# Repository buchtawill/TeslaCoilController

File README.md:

# TeslaCoilController
Forked from Cather-Zhang:TeslaCoilController to support new spin of interrupter.

STM32 tesla coil controller
Up to 5 notes simultaneously reading from custom binary file format

There are three modes available:
1. SD card (read songs from SD card)
2. Burst mode
3. Fixed mode

MIT License

Copyright (c) 2023 Will Buchta, Cather Zhang

Permission is hereby granted, free of charge, to any person obtaining a copy
of this software and associated documentation files (the "Software"), to deal
in the Software without restriction, including without limitation the rights
to use, copy, modify, merge, publish, distribute, sublicense, and/or sell
copies of the Software, and to permit persons to whom the Software is
furnished to do so, subject to the following conditions:

The above copyright notice and this permission notice shall be included in all
copies or substantial portions of the Software.

THE SOFTWARE IS PROVIDED "AS IS", WITHOUT WARRANTY OF ANY KIND, EXPRESS OR
IMPLIED, INCLUDING BUT NOT LIMITED TO THE WARRANTIES OF MERCHANTABILITY,
FITNESS FOR A PARTICULAR PURPOSE AND NONINFRINGEMENT. IN NO EVENT SHALL THE
AUTHORS OR COPYRIGHT HOLDERS BE LIABLE FOR ANY CLAIM, DAMAGES OR OTHER
LIABILITY, WHETHER IN AN ACTION OF CONTRACT, TORT OR OTHERWISE, ARISING FROM,
OUT OF OR IN CONNECTION WITH THE SOFTWARE OR THE USE OR OTHER DEALINGS IN THE
SOFTWARE.

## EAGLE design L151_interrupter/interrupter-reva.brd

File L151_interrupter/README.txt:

Directory structure:
    - Core/         STM32 specific drivers
    - Debug/        STM32 build debug dir
    - Drivers/      STM32 HAL drivers 
    - FATFS/        FATFS used for STM32 SD card
    - fusion360/    Interrupter case 3d files
    - Middlewares/  FATFS and USB stuff
    - USB_DEVICE/   STM32 USB drivers

Important notes:
    The program assumes that the SD card has .will formatted files in two directories:
        - single_coil/
        - dual_coils/
    Upon boot, the STM32 reads and stores all filenames from both these directories.
    Filenames are limited to 64 characters, including extension
    Up to 32 files can be in each directory (Fix this in the future)

    Need to enable "#define _FS_RPATH 1" in L151_interrupter\FATFS\Target\ffconf.h to enable "chdir()" function

    Setting A sets ONLY A 
    But setting B sets a and B

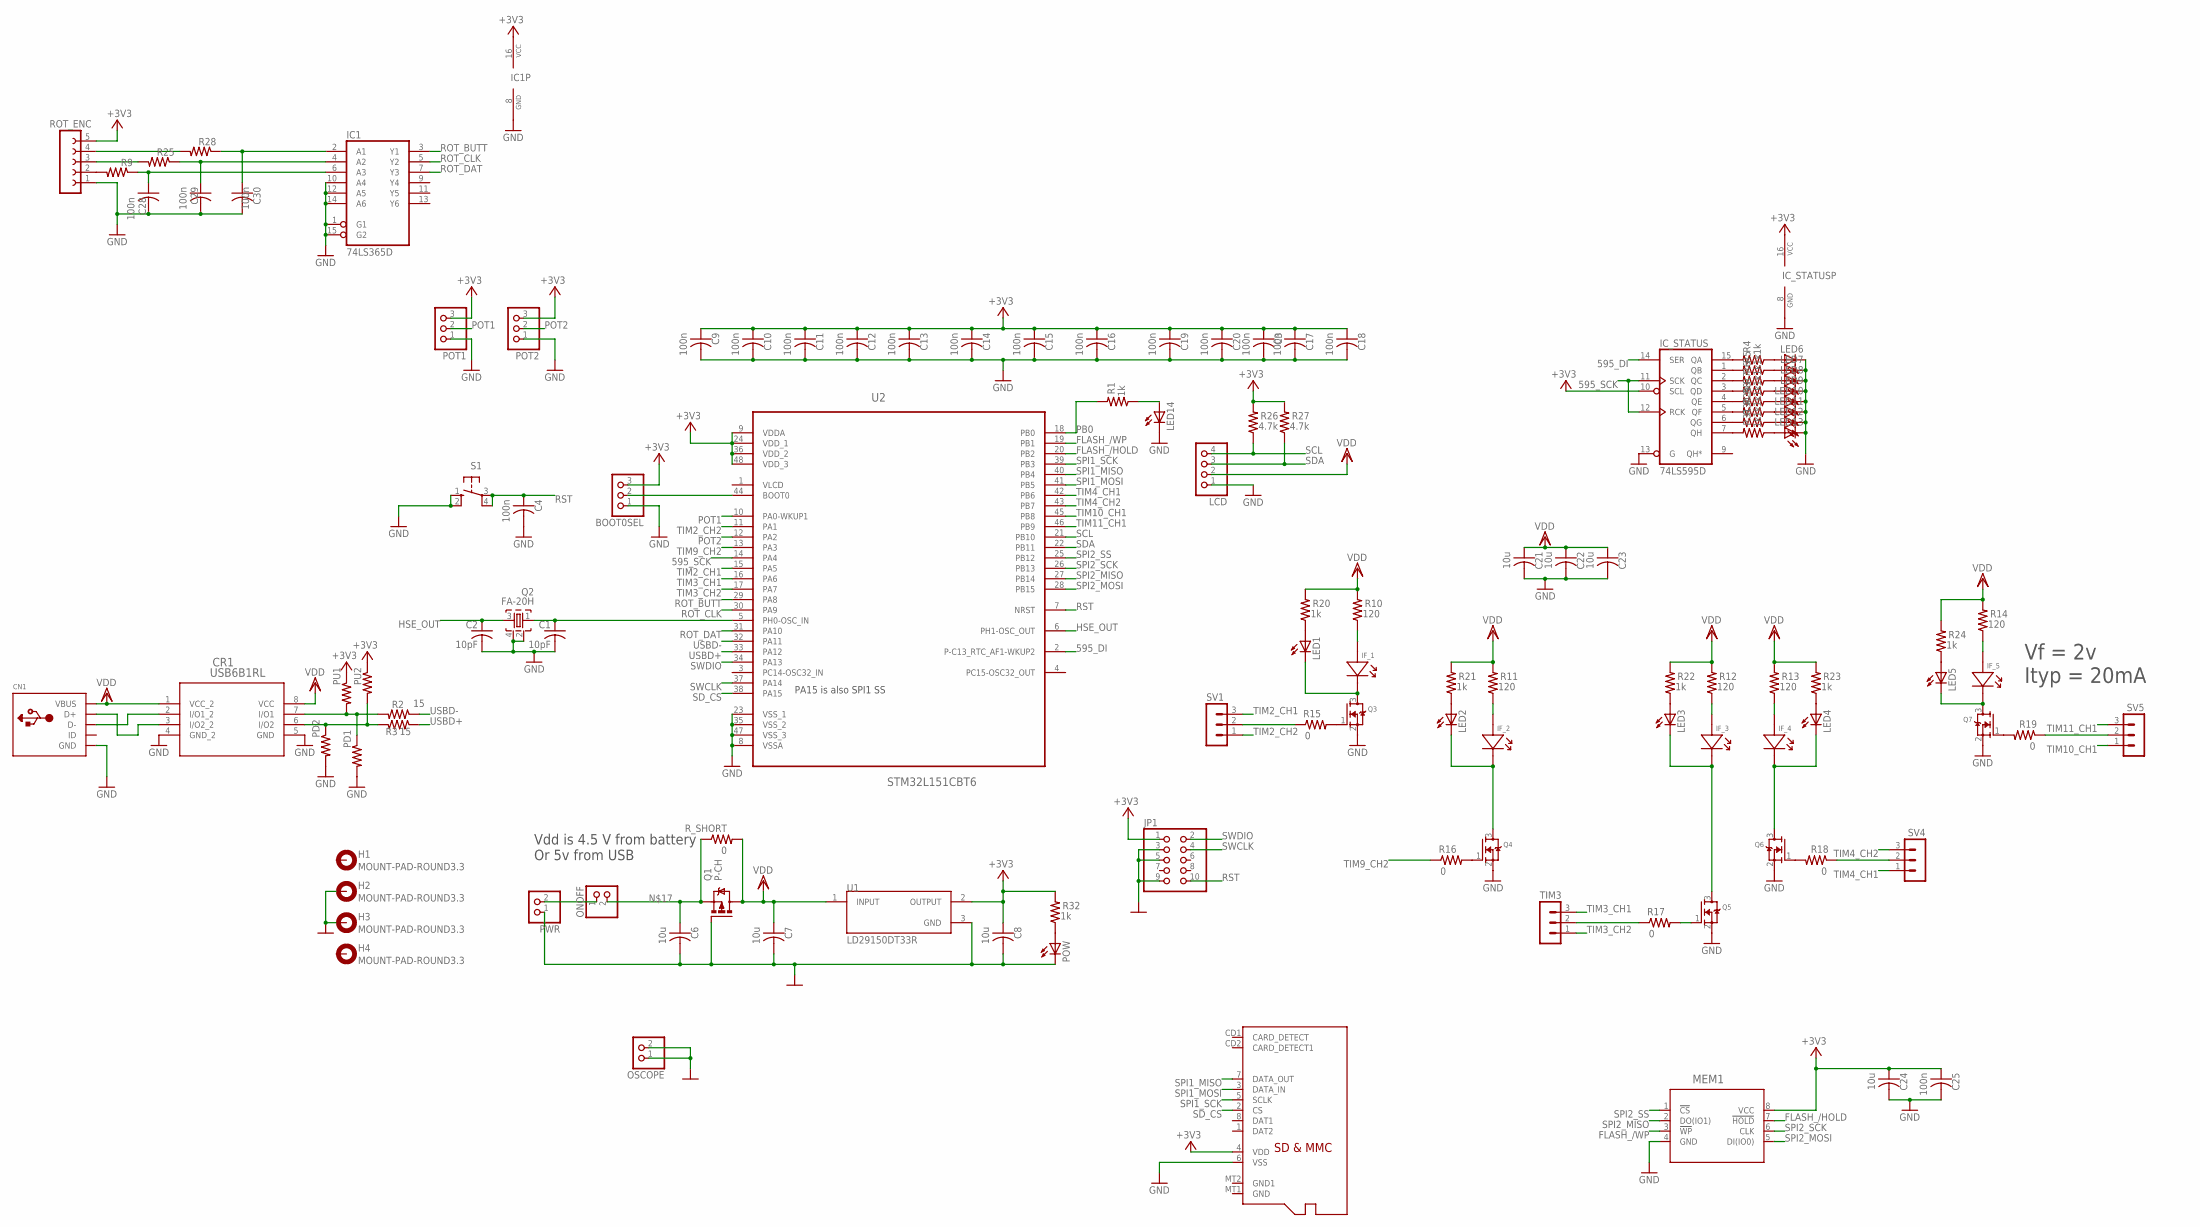
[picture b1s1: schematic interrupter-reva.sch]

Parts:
BOOT0SEL: PINHD-1X3; 1X03
C1, C2: 10pF; C0603
C3, C9, C11, C13, C15, C17, C20, C25: 100n; C0805
C4: 100n; C0402
C6, C7, C21, C22, C23: 10u; C0805
C8, C24: 10u; C0603
C10, C12, C14, C16, C18, C19, C28, C29, C30: 100n; C0603
CN1: USBMINIB; USB-MINIB
CR1: USB6B1RL; SO-8_STM
H1, H2, H3, H4: MOUNT-PAD-ROUND3.3; 3,3-PAD
IC1: 74LS365D; SO16
IC_STATUS: 74LS595D; SO16
IF_1, IF_2, IF_3, IF_4, IF_5: IF-E96E
JP1: PINHD-2X5; 2X05
LCD: PINHD-1X4; 1X04
LED1, LED2, LED3, LED4, LED5, LED6, LED7, LED8, LED9, LED10, LED11, LED12, LED13, LED14: LEDCHIP-LED0805; CHIP-LED0805
MEM1: W25X40CLSNIG; WIN_SN-8_WIN
ONOFF: PINHD-1X2; 1X02
OSCOPE: PINHD-1X2; 1X02
PD1, PD2: 15; R0603
POT1, POT2: PINHD-1X3; 1X03
POW: LEDCHIP-LED0805; CHIP-LED0805
PU1, PU2: 15; R0603
PWR: PINHD-1X2; 1X02
Q1: P-CH; MICRO3
Q2: FA-20H
Q3, Q4, Q5, Q6, Q7: MOSFET-NREFLOW; SOT23
R1, R4, R5, R6, R7, R8, R29, R30, R31, R32: 1k; R0603
R2, R3: 15; R0603
R9, R25, R28: R-US_R0603; R0603
R10, R11, R12, R13, R14: 120; R0805
R15, R16, R17, R18, R19: 0; R0805
R20, R21, R22, R23, R24: 1k; R0805
R26, R27: 4.7k; R0805
ROT_ENC: FE05-1
R_SHORT: 0; R0805
S1: 10-XX; B3F-10XX
SV1, SV4, SV5: MA03-1
TIM3: MA03-1
U1: LD29150DT33R; DPAK456P972X240-3N
U2: STM32L151CBT6; QFP50P900X900X160-48N
U$1: MICROSD

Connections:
595_DI: IC_STATUS.14 (SER), U2.2 (P-C13_RTC_AF1-WKUP2)
595_SCK: IC_STATUS.11 (SCK), IC_STATUS.12 (RCK), U2.14 (PA4)
+3V3: BOOT0SEL.3, C3.1, C8.1, C9.1, C10.1, C11.1, C12.1, C13.1, C14.1, C15.1, C16.1, C17.1, C18.1, C19.1, C20.1, C24.1, C25.1, IC1.16 (VCC), IC_STATUS.10 (SCL), IC_STATUS.16 (VCC), JP1.1, MEM1.8 (VCC), POT1.3, POT2.3, PU1.1, PU2.1, R26.2, R27.2, R32.2, ROT_ENC.5, U1.2 (OUTPUT), U2.9 (VDDA), U2.24 (VDD_1), U2.36 (VDD_2), U2.48 (VDD_3), U$1.4 (VDD)
FLASH_/HOLD: MEM1.7 (!HOLD), U2.20 (PB2)
FLASH_/WP: MEM1.3 (!WP), U2.19 (PB1)
GND: BOOT0SEL.1, C1.2, C2.2, C3.2, C4.2, C6.2, C7.2, C8.2, C9.2, C10.2, C11.2, C12.2, C13.2, C14.2, C15.2, C16.2, C17.2, C18.2, C19.2, C20.2, C21.2, C22.2, C23.2, C24.2, C25.2, C28.2, C29.2, C30.2, CN1.GND, CR1.4 (GND_2), CR1.5 (GND), H2.B3,3, H3.B3,3, IC1.1 (G1), IC1.8 (GND), IC1.10 (A4), IC1.12 (A5), IC1.14 (A6), IC1.15 (G2), IC_STATUS.8 (GND), IC_STATUS.13 (G), JP1.3, JP1.5, JP1.9, LCD.1, LED6.C, LED7.C, LED8.C, LED9.C, LED10.C, LED11.C, LED12.C, LED13.C, LED14.C, MEM1.4 (GND), OSCOPE.1, OSCOPE.2, PD1.2, PD2.2, POT1.1, POT2.1, POW.C, PWR.1, Q1.1 (G), Q2.2, Q2.4, Q3.2 (S), Q4.2 (S), Q5.2 (S), Q6.2 (S), Q7.2 (S), ROT_ENC.1, S1.1 (S), S1.2 (S1), U1.3 (GND), U2.8 (VSSA), U2.23 (VSS_1), U2.35 (VSS_2), U2.47 (VSS_3), U$1.6 (VSS)
HSE_OUT: C2.1, Q2.3, U2.6 (PH1-OSC_OUT)
unnamed: R9.2, ROT_ENC.2
unnamed: LED1.A, R20.1
unnamed: CN1.D-, CR1.2 (I/O1_2)
unnamed: LED2.A, R21.1
unnamed: LED3.A, R22.1
unnamed: LED5.A, R24.1
unnamed: IF_1.ANODE, R10.1
unnamed: IF_2.ANODE, R11.1
unnamed: IF_3.ANODE, R12.1
unnamed: IF_4.ANODE, R13.1
unnamed: IF_5.ANODE, R14.1
unnamed: IF_1.CATHODE, LED1.C, Q3.3 (D)
unnamed: IF_2.CATHODE, LED2.C, Q4.3 (D)
unnamed: IF_3.CATHODE, LED3.C, Q5.3 (D)
unnamed: IF_4.CATHODE, LED4.C, Q6.3 (D)
unnamed: IF_5.CATHODE, LED5.C, Q7.3 (D)
unnamed: C6.1, ONOFF.2, Q1.2 (S), R_SHORT.1
unnamed: ONOFF.1, PWR.2
unnamed: CN1.D+, CR1.3 (I/O2_2)
unnamed: CR1.7 (I/O1), PD1.1, PU1.2, R2.2
unnamed: R25.2, ROT_ENC.3
unnamed: Q7.1 (G), R19.2
unnamed: R28.2, ROT_ENC.4
unnamed: CR1.6 (I/O2), PD2.1, PU2.2, R3.2
unnamed: LED4.A, R23.1
unnamed: C28.1, IC1.6 (A3), R9.1
unnamed: C29.1, IC1.4 (A2), R25.1
unnamed: C30.1, IC1.2 (A1), R28.1
unnamed: LED6.A, R4.1
unnamed: IC_STATUS.15 (QA), R4.2
unnamed: C1.1, Q2.1, U2.5 (PH0-OSC_IN)
unnamed: LED7.A, R5.1
unnamed: IC_STATUS.1 (QB), R5.2
unnamed: LED8.A, R6.1
unnamed: IC_STATUS.2 (QC), R6.2
unnamed: LED9.A, R7.1
unnamed: IC_STATUS.3 (QD), R7.2
unnamed: LED10.A, R8.1
unnamed: IC_STATUS.4 (QE), R8.2
unnamed: LED11.A, R29.1
unnamed: IC_STATUS.5 (QF), R29.2
unnamed: LED12.A, R30.1
unnamed: IC_STATUS.6 (QG), R30.2
unnamed: BOOT0SEL.2, U2.44 (BOOT0)
unnamed: R15.1, SV1.2
unnamed: Q3.1 (G), R15.2
unnamed: Q4.1 (G), R16.2
unnamed: LED13.A, R31.1
unnamed: Q5.1 (G), R17.2
unnamed: R17.1, TIM3.2
unnamed: Q6.1 (G), R18.2
unnamed: R18.1, SV4.2
unnamed: R19.1, SV5.2
unnamed: IC_STATUS.7 (QH), R31.2
unnamed: LED14.A, R1.1
unnamed: POW.A, R32.1
PB0: R1.2, U2.18 (PB0)
POT1: POT1.2, U2.10 (PA0-WKUP1)
POT2: POT2.2, U2.12 (PA2)
ROT_BUTT: IC1.3 (Y1), U2.29 (PA8)
ROT_CLK: IC1.5 (Y2), U2.30 (PA9)
ROT_DAT: IC1.7 (Y3), U2.31 (PA10)
RST: C4.1, JP1.10, S1.3, S1.4 (P1), U2.7 (NRST)
SCL: LCD.4, R26.1, U2.21 (PB10)
SDA: LCD.3, R27.1, U2.22 (PB11)
SD_CS: U2.38 (PA15), U$1.2 (CS)
SPI1_MISO: U2.40 (PB4), U$1.7 (DATA_OUT)
SPI1_MOSI: U2.41 (PB5), U$1.3 (DATA_IN)
SPI1_SCK: U2.39 (PB3), U$1.5 (SCLK)
SPI2_MISO: MEM1.2 (DO(IO1)), U2.27 (PB14)
SPI2_MOSI: MEM1.5 (DI(IO0)), U2.28 (PB15)
SPI2_SCK: MEM1.6 (CLK), U2.26 (PB13)
SPI2_SS: MEM1.1 (!CS), U2.25 (PB12)
SWCLK: JP1.4, U2.37 (PA14)
SWDIO: JP1.2, U2.34 (PA13)
TIM2_CH1: SV1.3, U2.15 (PA5)
TIM2_CH2: SV1.1, U2.11 (PA1)
TIM3_CH1: TIM3.3, U2.16 (PA6)
TIM3_CH2: TIM3.1, U2.17 (PA7)
TIM4_CH1: SV4.1, U2.42 (PB6)
TIM4_CH2: SV4.3, U2.43 (PB7)
TIM9_CH2: R16.1, U2.13 (PA3)
TIM10_CH1: SV5.1, U2.45 (PB8)
TIM11_CH1: SV5.3, U2.46 (PB9)
USBD+: R3.1, U2.33 (PA12)
USBD-: R2.1, U2.32 (PA11)
VDD: C7.1, C21.1, C22.1, C23.1, CN1.VBUS, CR1.1 (VCC_2), CR1.8 (VCC), LCD.2, Q1.3 (D), R10.2, R11.2, R12.2, R13.2, R14.2, R20.2, R21.2, R22.2, R23.2, R24.2, R_SHORT.2, U1.1 (INPUT)
VLCD: U2.1 (VLCD)

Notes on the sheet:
Vf = 2v Ityp = 20mA
Vdd is 4.5 V from battery Or 5v from USB
PA15 is also SPI1 SS

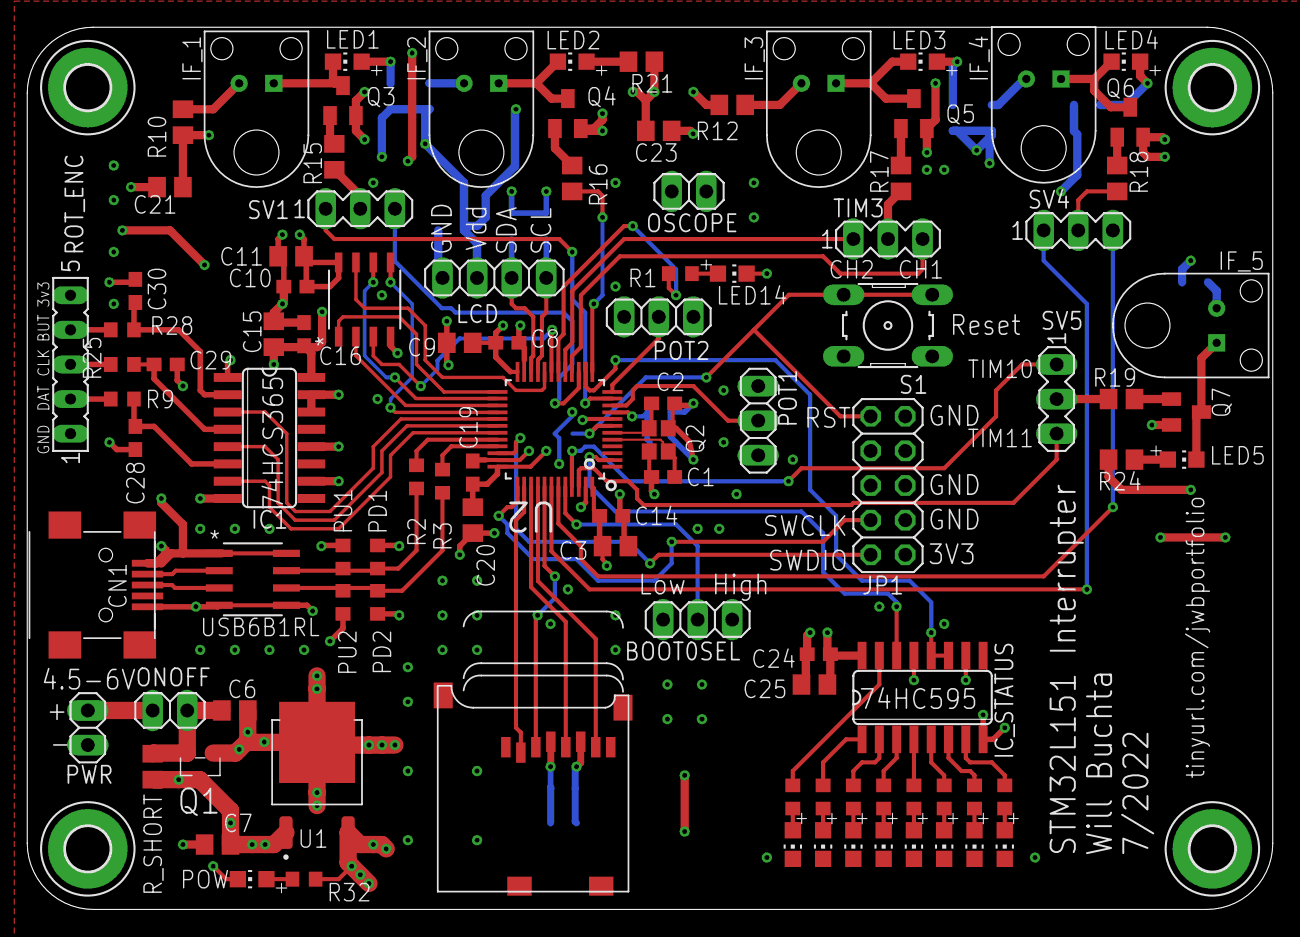
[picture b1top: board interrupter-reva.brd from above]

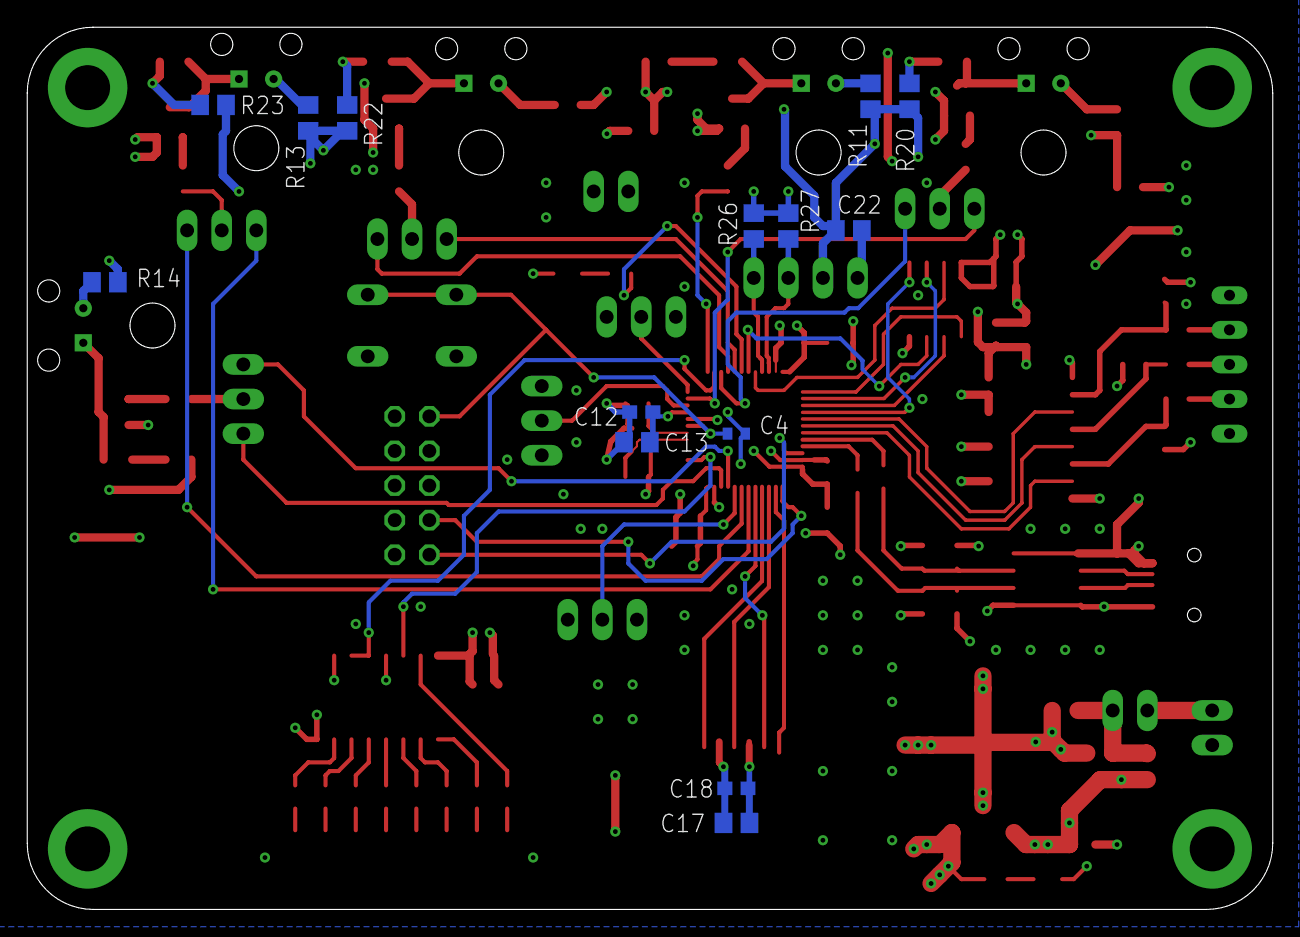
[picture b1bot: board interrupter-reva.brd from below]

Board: 4 copper layers, 91.4 x 64.8 mm, 117 parts (14 on the bottom side), 94 nets.

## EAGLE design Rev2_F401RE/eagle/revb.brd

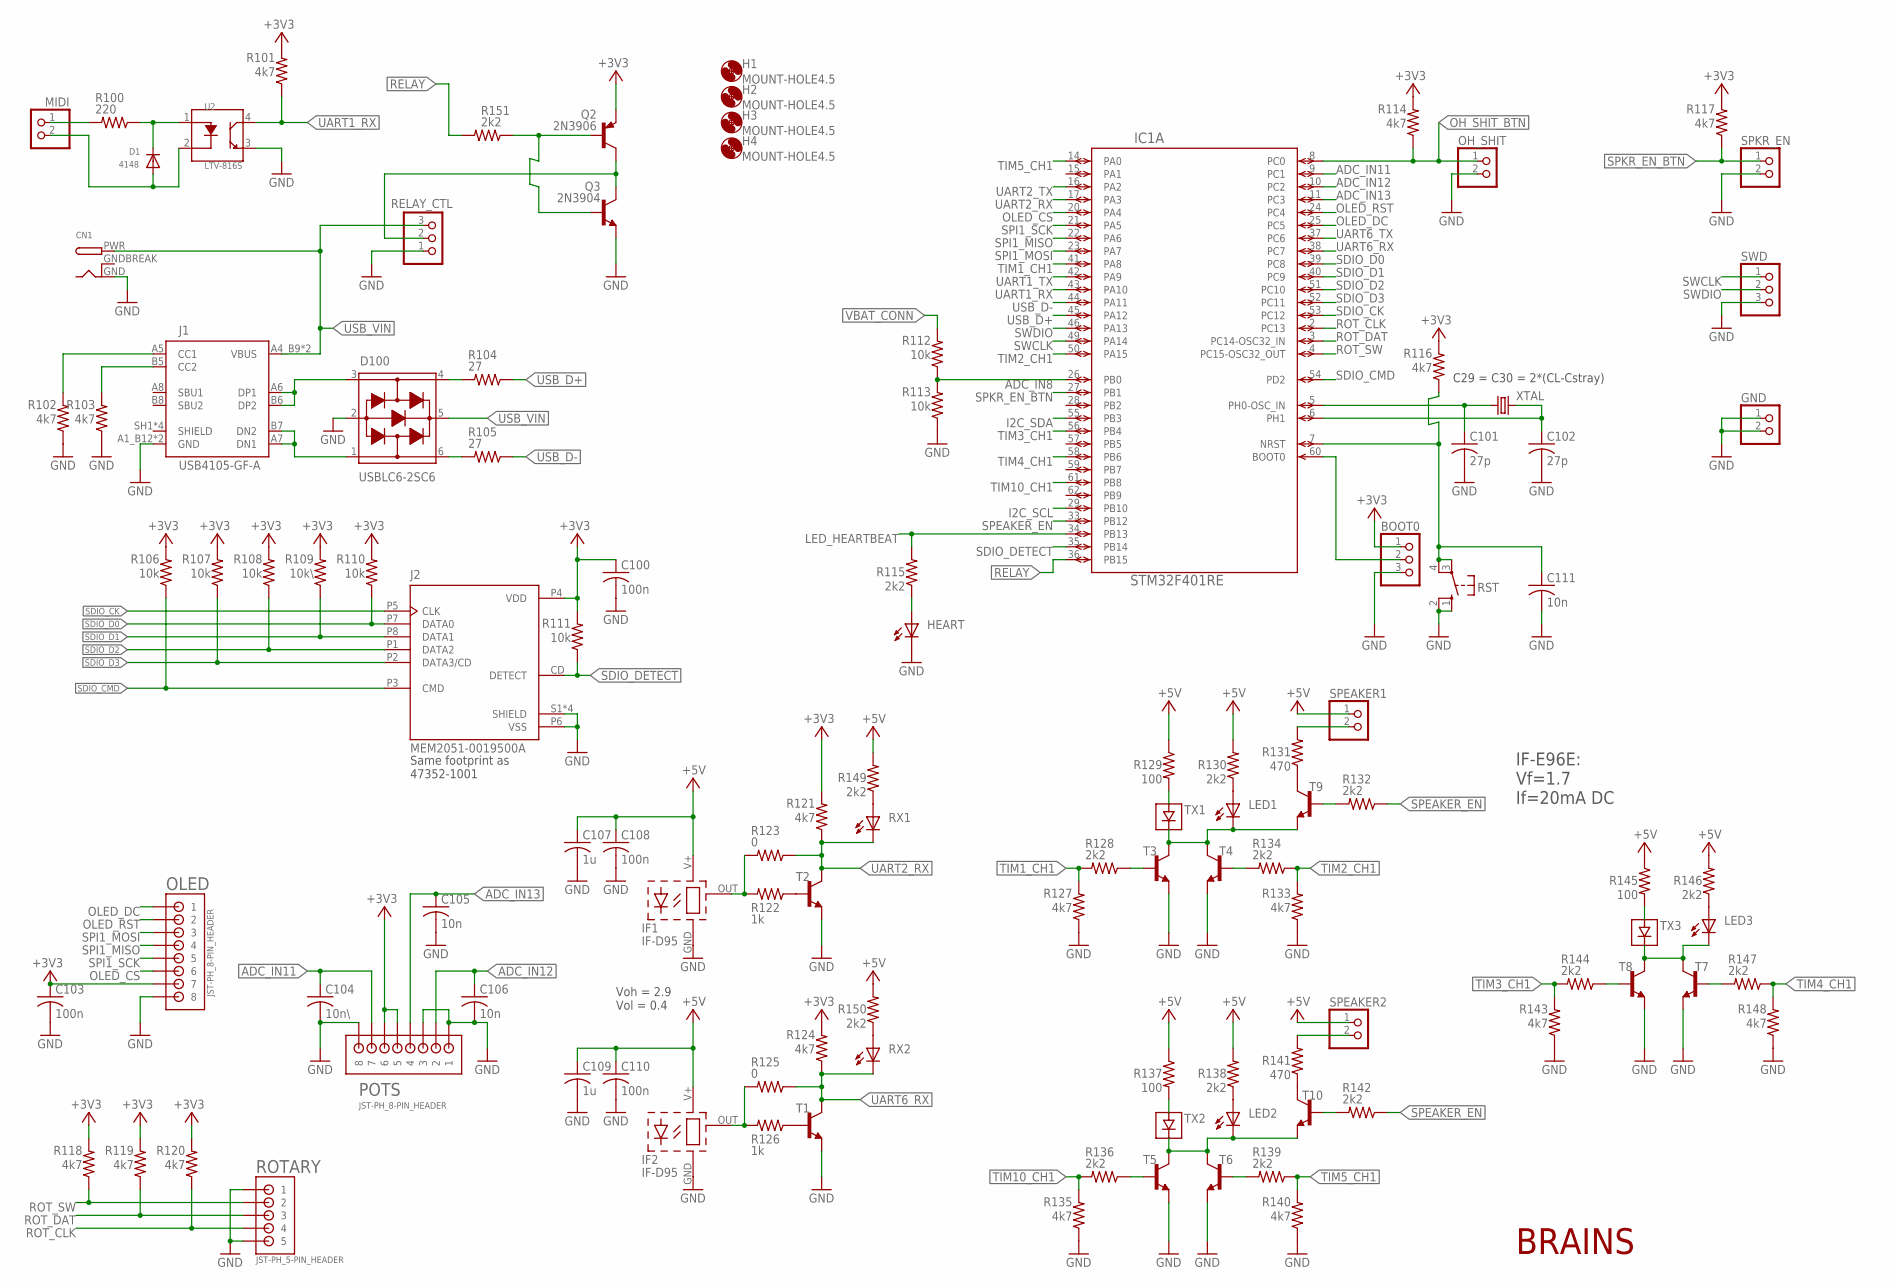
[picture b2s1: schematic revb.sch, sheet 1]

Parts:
BOOT0: PINHD-1X3; 1X03
C100, C103, C108, C110: 100n; C0603K
C101, C102: 27p; C0402
C104: 10n\; C0603K
C105, C106, C111: 10n; C0603K
C107, C109: 1u; C0603K
CN1: DCBARRELPTH; DCJACK_2MM_PTH
D1: 4148; SOD-123
D100: USBLC6-2SC6; SOT95P280X145-6N
GND: PINHD-1X2; 1X02
H1, H2, H3, H4: MOUNT-HOLE4.5; 4,5
HEART: LEDCHIPLED_0805; CHIPLED_0805
IC1: STM32F401RE; LQFP64-10X10MM
IF1, IF2: IF-D95; IFD95
J1: USB4105-GF-A; GCT_USB4105-GF-A
J2: MEM2051-0019500A; GCT_MEM2051-00-195-00-A_REVD1
LED1, LED2, LED3: LEDCHIPLED_0805; CHIPLED_0805
MIDI: PINHD-1X2; 1X02
OH_SHIT: PINHD-1X2; 1X02
OLED: JST-PH_8-PIN_HEADER; JST_B8B-PH_HEADER
POTS: JST-PH_8-PIN_HEADER; JST_B8B-PH_HEADER
Q2: 2N3906; TO92
Q3: 2N3904; TO92
R100: 220; R0603
R101, R102, R103, R114, R116, R117, R118, R119, R120, R121, R124, R127, R133, R135, R140, R143, R148: 4k7; R0603
R104, R105: 27; R0603
R106, R107, R108, R110, R111, R112, R113: 10k; R0805
R109: 10k\; R0805
R115, R128, R130, R132, R134, R136, R138, R139, R142, R144, R146, R147, R149, R150, R151: 2k2; R0603
R122, R126: 1k; R0805
R123, R125: 0; R0603
R129, R137, R145: 100; R0805
R131, R141: 470; R0603
RELAY_CTL: PINHD-1X3; 1X03
ROTARY: JST-PH_5-PIN_HEADER; JST_B5B-PH_HEADER
RST: 10-XX; B3F-10XX
RX1, RX2: LEDCHIPLED_0805; CHIPLED_0805
SPEAKER1, SPEAKER2: PINHD-1X2; 1X02
SPKR_EN: PINHD-1X2; 1X02
SWD: PINHD-1X3; 1X03
T1, T2, T3, T4, T5, T6, T7, T8, T9, T10: MMBTA06-7-F; SOT23-BEC
TX1, TX2, TX3: IF-E95E; IF-E96E
U2: LTV-816S; SMD4-2.54-4.6X6.5MM
XTAL: CRYSTALHC49S; HC49/S

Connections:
+3V3: BOOT0.1, C100.1, C103.1, J2.P4 (VDD), OLED.P7 (7), POTS.P5 (5), POTS.P6 (6), Q2.3 (E), R101.2, R106.2, R107.2, R108.2, R109.2, R110.2, R111.2, R114.2, R116.2, R117.2, R118.2, R119.2, R120.2, R121.2, R124.2; also elsewhere on the board
+5V: C107.1, C108.1, C109.1, C110.1, IF1.V+ (VCC), IF2.V+ (VCC), R129.1, R130.2, R137.1, R138.2, R145.1, R146.2, R149.2, R150.2, SPEAKER1.1, SPEAKER2.1; also elsewhere on the board
ADC_IN8: IC1.26 (PB0), R112.1, R113.2
ADC_IN11: C104.1, IC1.9 (PC1), POTS.P7 (7)
ADC_IN12: C106.1, IC1.10 (PC2), POTS.P2 (2)
ADC_IN13: C105.1, IC1.11 (PC3), POTS.P4 (4)
BOOT0_CONN: BOOT0.2, IC1.60 (BOOT0)
CC1: J1.A5 (CC1), R102.2
CC2: J1.B5 (CC2), R103.2
COIL1_B: R128.1, T3.B
COIL1_NEG: LED1.C, T3.C, T4.C, T9.E, TX1.GND
COIL1_POS: R129.2, TX1.SIG
COIL2_B: R136.1, T5.B
COIL2_NEG: LED2.C, T5.C, T6.C, T10.E, TX2.GND
COIL2_POS: R137.2, TX2.SIG
COIL3_B: R144.1, T8.B
COIL3_NEG: LED3.C, T7.C, T8.C, TX3.GND
COIL3_POS: R145.2, TX3.SIG
COIL12_B: R134.2, T4.B
COIL22_B: R139.2, T6.B
COIL32_B: R147.2, T7.B
GND: BOOT0.3, C100.2, C101.2, C102.2, C103.2, C104.2, C105.2, C106.2, C107.2, C108.2, C109.2, C110.2, C111.2, CN1.GND, D100.2 (GND), GND.1, GND.2, HEART.C, IF1.GND, IF2.GND, J1.A1_B12 (GND), J1.B1_A12 (GND), J2.P6 (VSS), J2.S1 (SHIELD), J2.S2 (SHIELD), J2.S3 (SHIELD), J2.S4 (SHIELD), OH_SHIT.2, OLED.P8 (8), POTS.P1 (1), POTS.P3 (3), POTS.P8 (8), Q3.3 (E), R102.1, R103.1, R113.1, R127.1, R133.1, R135.1, R140.1, R143.1, R148.1, RELAY_CTL.1, ROTARY.P1 (1), ROTARY.P5 (5), RST.1 (S), RST.2 (S1), SPKR_EN.2, SWD.3, T1.E, T2.E, T3.E, T4.E, T5.E, T6.E, T7.E, T8.E, U2.3 (EMITER); also elsewhere on the board
GNDBREAK: CN1.GNDBREAK
I2C_SCL: IC1.29 (PB10); also elsewhere on the board
I2C_SDA: IC1.55 (PB3); also elsewhere on the board
IF1-OUT: IF1.OUT, R122.2, R123.2
IF2-OUT: IF2.OUT, R125.2, R126.2
LED_HEARTBEAT: IC1.34 (PB13), R115.2
LTV+: D1.C, R100.1, U2.1 (ANODE)
LTV-: D1.A, MIDI.2, U2.2 (CATHODE)
MID_RX_IN: MIDI.1, R100.2
unnamed: LED1.A, R130.1
unnamed: R122.1, T2.B
unnamed: LED3.A, R146.1
unnamed: LED2.A, R138.1
unnamed: R149.1, RX1.A
unnamed: R150.1, RX2.A
unnamed: R126.1, T1.B
unnamed: R131.1, T9.C
unnamed: R141.1, T10.C
NRST: C111.1, IC1.7 (NRST), R116.1, RST.3, RST.4 (P1)
OH_SHIT_BTN: IC1.8 (PC0), OH_SHIT.1, R114.1
OLED_CS: IC1.20 (PA4), OLED.P6 (6)
OLED_DC: IC1.25 (PC5), OLED.P1 (1)
OLED_RST: IC1.24 (PC4), OLED.P2 (2)
R-HB: HEART.A, R115.1
RELAY: IC1.36 (PB15), R151.2
RELAY_OUT: Q2.1 (C), Q3.1 (C), RELAY_CTL.2
RLY_BASE: Q2.2 (B), Q3.2 (B), R151.1
ROT_CLK: IC1.2 (PC13), R120.1, ROTARY.P4 (4)
ROT_DAT: IC1.3 (PC14-OSC32_IN), R119.1, ROTARY.P3 (3)
ROT_SW: IC1.4 (PC15-OSC32_OUT), R118.1, ROTARY.P2 (2)
SDIO_CK: IC1.53 (PC12), J2.P5 (CLK)
SDIO_CMD: IC1.54 (PD2), J2.P3 (CMD), R106.1
SDIO_D0: IC1.39 (PC8), J2.P7 (DATA0), R110.1
SDIO_D1: IC1.40 (PC9), J2.P8 (DATA1), R109.1
SDIO_D2: IC1.51 (PC10), J2.P1 (DATA2), R108.1
SDIO_D3: IC1.52 (PC11), J2.P2 (DATA3/CD), R107.1
SDIO_DETECT: IC1.35 (PB14), J2.CD (DETECT), R111.1
SHIELD: J1.SH1 (SHIELD), J1.SH2 (SHIELD), J1.SH3 (SHIELD), J1.SH4 (SHIELD)
SPEAK1-R: R131.2, SPEAKER1.2
SPEAKER_EN: IC1.33 (PB12), R132.1, R142.1
SPI1_MISO: IC1.22 (PA6), OLED.P4 (4)
SPI1_MOSI: IC1.23 (PA7), OLED.P3 (3)
SPI1_SCK: IC1.21 (PA5), OLED.P5 (5)
SPK2_R: R141.2, SPEAKER2.2
SPKR_EN_BTN: IC1.27 (PB1), R117.1, SPKR_EN.1
SPK_EN1_B: R132.2, T9.B
SPK_EN2_B: R142.2, T10.B
SWCLK: IC1.49 (PA14), SWD.1
SWDIO: IC1.46 (PA13), SWD.2
TIM1_CH1: IC1.41 (PA8), R127.2, R128.2
TIM2_CH1: IC1.50 (PA15), R133.2, R134.1
TIM3_CH1: IC1.56 (PB4), R143.2, R144.2
TIM4_CH1: IC1.58 (PB6), R147.1, R148.2
TIM5_CH1: IC1.14 (PA0), R139.1, R140.2
TIM10_CH1: IC1.61 (PB8), R135.2, R136.2
UART1_RX: IC1.43 (PA10), R101.1, U2.4 (COLLECTOR)
UART1_TX: IC1.42 (PA9)
UART2_RX: IC1.17 (PA3), R121.1, R123.1, RX1.C, T2.C
UART2_TX: IC1.16 (PA2)
UART6_RX: IC1.38 (PC7), R124.1, R125.1, RX2.C, T1.C
UART6_TX: IC1.37 (PC6)
USBDN_CONN: D100.1 (I/O1_IN), J1.A7 (DN1), J1.B7 (DN2)
USBDP_CONN: D100.3 (I/O2_IN), J1.A6 (DP1), J1.B6 (DP2)
USBRESD_N: D100.6 (I/O1_OUT), R105.2
USBRESD_P: D100.4 (I/O2_OUT), R104.2
USB_D+: IC1.45 (PA12), R104.1
USB_D-: IC1.44 (PA11), R105.1
USB_VIN: CN1.PWR, D100.5 (VBUS), J1.A4_B9 (VBUS), J1.B4_A9 (VBUS), RELAY_CTL.3; also elsewhere on the board
VBAT_CONN: R112.2; also elsewhere on the board
XTAL1: C101.1, IC1.5 (PH0-OSC_IN), XTAL.1
XTAL2: C102.1, IC1.6 (PH1), XTAL.2

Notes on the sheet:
BRAINS
C29 = C30 = 2*(CL-Cstray)
IF-E96E: Vf=1.7 If=20mA DC
Voh = 2.9 Vol = 0.4
Same footprint as 47352-1001

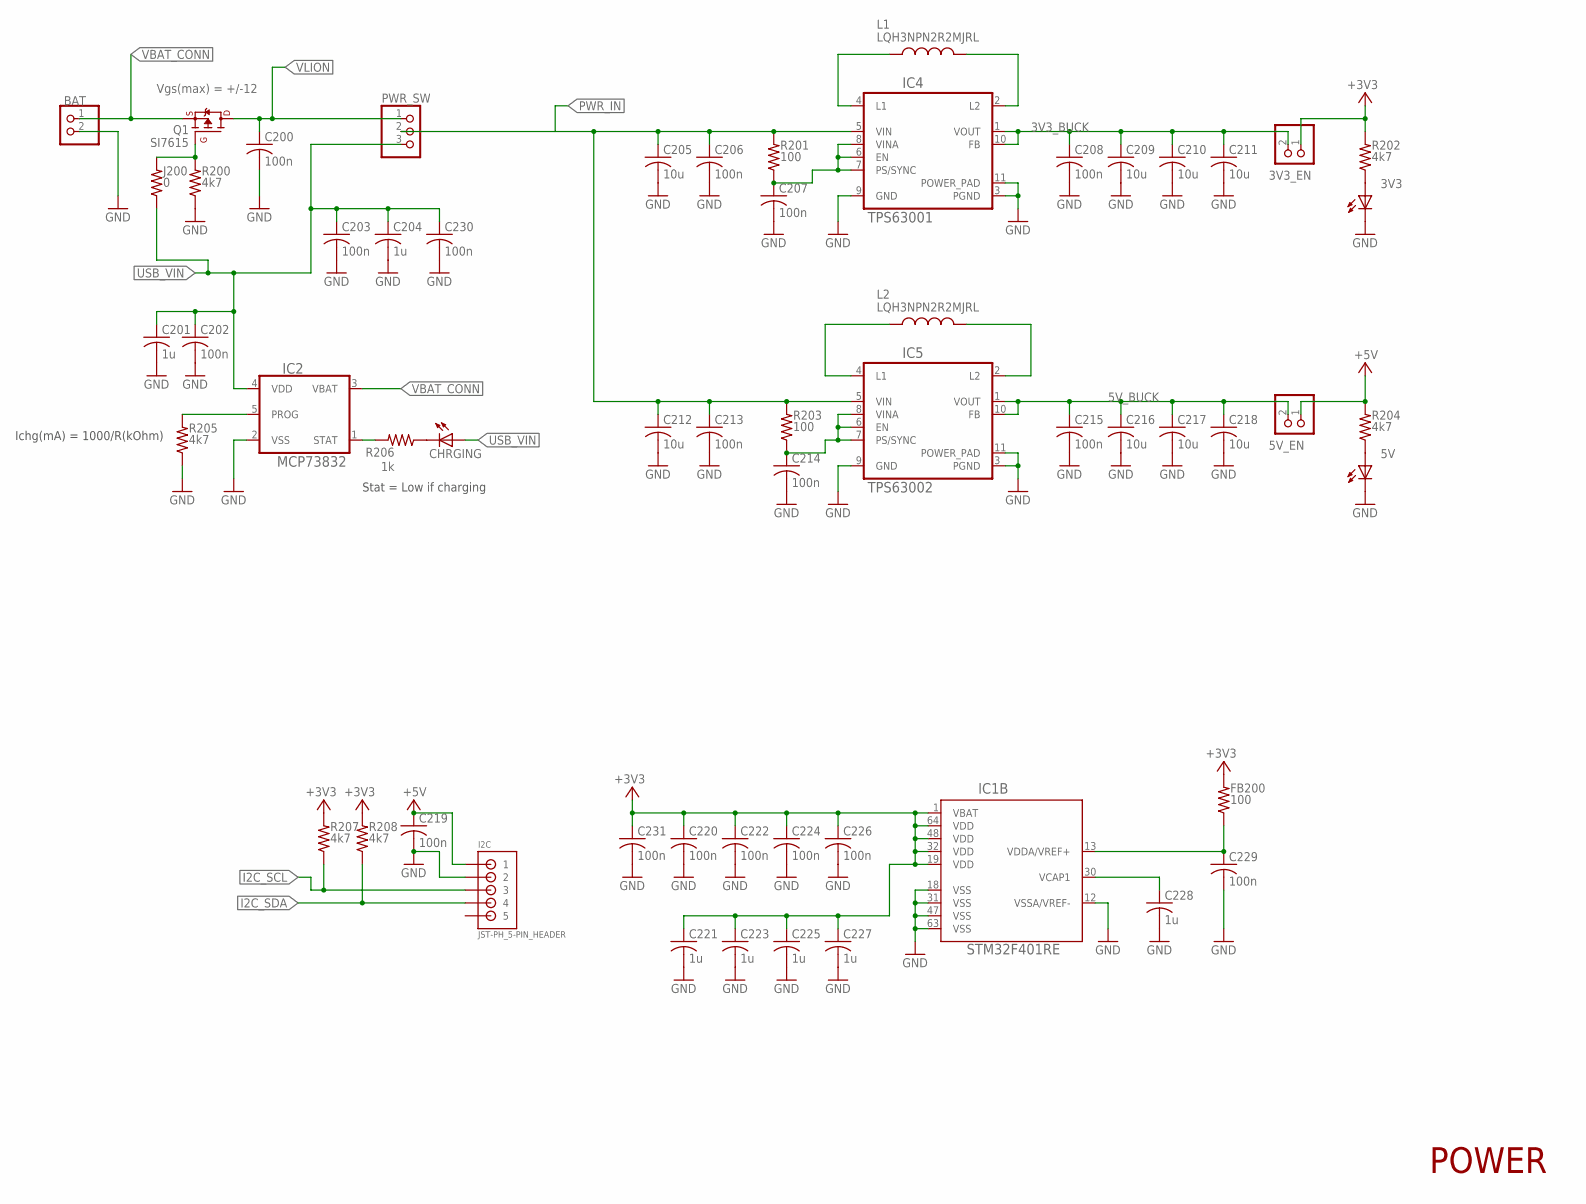
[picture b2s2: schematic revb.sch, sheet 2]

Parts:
3V3, 5V: LEDCHIPLED_0603; CHIPLED_0603
3V3_EN, 5V_EN: PINHD-1X2; 1X02
BAT: JST_2PIN-THM; JST-PH-2-THM
C200, C202, C203, C206, C207, C208, C213, C214, C215, C219, C220, C222, C224, C226, C229, C230, C231: 100n; C0603K
C201, C204, C221, C223, C225, C227, C228: 1u; C0603K
C205, C209, C210, C211, C212, C216, C217, C218: 10u; C0805
CHRGING: LEDCHIPLED_1206; CHIPLED_1206
FB200: 100; R0603
I2C: JST-PH_5-PIN_HEADER; JST_B5B-PH_HEADER
IC1: STM32F401RE; LQFP64-10X10MM
IC2: MCP73832; SOT95P280X145-5N
IC4: TPS63001; VREG_V62/16624-01YE
IC5: TPS63002; VREG_V62/16624-01YE
J200: 0; R0402
L1, L2: LQH3NPN2R2MJRL; IND_LQH3NPN2R2MJRL
PWR_SW: PINHD-1X3; 1X03
Q1: SI7615; VISHAY_SIS468DN-T1-GE3
R200, R202, R204, R205, R207, R208: 4k7; R0603
R201, R203: 100; R0603
R206: 1k; R0603

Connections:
3V3_BUCK: 3V3_EN.2, C208.1, C209.1, C210.1, C211.1, IC4.1 (VOUT), IC4.10 (FB)
5V_BUCK: 5V_EN.2, C215.1, C216.1, C217.1, C218.1, IC5.1 (VOUT), IC5.10 (FB)
+3V3: 3V3_EN.1, C220.1, C221.1, C222.1, C223.1, C224.1, C225.1, C226.1, C227.1, C231.1, FB200.2, IC1.1 (VBAT), IC1.19 (VDD), IC1.32 (VDD), IC1.48 (VDD), IC1.64 (VDD), R202.2, R207.2, R208.2; also elsewhere on the board
+5V: 5V_EN.1, C219.1, I2C.P1 (1), R204.2; also elsewhere on the board
BUCK33_LOGIC: C207.1, IC4.6 (EN), IC4.7 (PS/SYNC), IC4.8 (VINA), R201.1
BUCK50_LOGIC: C214.1, IC5.6 (EN), IC5.7 (PS/SYNC), IC5.8 (VINA), R203.1
CHG_PROG: IC2.5 (PROG), R205.2
CHRG_STAT: IC2.1 (STAT), R206.2
GND: 3V3.C, 5V.C, BAT.2 (1), C200.2, C201.2, C202.2, C203.2, C204.2, C205.2, C206.2, C207.2, C208.2, C209.2, C210.2, C211.2, C212.2, C213.2, C214.2, C215.2, C216.2, C217.2, C218.2, C219.2, C220.2, C221.2, C222.2, C223.2, C224.2, C225.2, C226.2, C227.2, C228.2, C229.2, C230.2, C231.2, I2C.P2 (2), IC1.12 (VSSA/VREF-), IC1.18 (VSS), IC1.31 (VSS), IC1.47 (VSS), IC1.63 (VSS), IC2.2 (VSS), IC4.3 (PGND), IC4.9 (GND), IC4.11 (POWER_PAD), IC5.3 (PGND), IC5.9 (GND), IC5.11 (POWER_PAD), R200.1, R205.1; also elsewhere on the board
I2C_SCL: I2C.P3 (3), R207.1; also elsewhere on the board
I2C_SDA: I2C.P4 (4), R208.1; also elsewhere on the board
IC4L1: IC4.4 (L1), L1.1
IC4L2: IC4.2 (L2), L1.2
IC5L1: IC5.4 (L1), L2.1
IC5L2: IC5.2 (L2), L2.2
unnamed: 3V3.A, R202.1
unnamed: 5V.A, R204.1
unnamed: CHRGING.C, R206.1
PMOS_G: J200.2, Q1.4 (G), R200.2
PWR_IN: C205.1, C206.1, C212.1, C213.1, IC4.5 (VIN), IC5.5 (VIN), PWR_SW.2, R201.2, R203.2
USB_VIN: C201.1, C202.1, C203.1, C204.1, C230.1, CHRGING.A, IC2.4 (VDD), J200.1, PWR_SW.3; also elsewhere on the board
VBAT_CONN: BAT.1 (2), IC2.3 (VBAT), Q1.1 (S), Q1.2 (S), Q1.3 (S); also elsewhere on the board
VCAP1: C228.1, IC1.30 (VCAP1)
VLION: C200.1, PWR_SW.1, Q1.5 (D), Q1.6 (D), Q1.7 (D), Q1.8 (D), Q1.9 (D)
VREF+: C229.1, FB200.1, IC1.13 (VDDA/VREF+)

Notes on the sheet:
POWER
Vgs(max) = +/-12
Stat = Low if charging
Ichg(mA) = 1000/R(kOhm)

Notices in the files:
L151_interrupter/Core/Src/stm32l1xx_hal_msp.c:
Copyright (c) 2022 STMicroelectronics.
All rights reserved.
This software is licensed under terms that can be found in the LICENSE file
parts and their libraries:
COPYRIGHT: Copyright (C) 2022 Ultra Librarian. All rights reserved.
COPYRIGHT: Copyright (C) 2024 Ultra Librarian. All rights reserved.
COPYRIGHT: Copyright (C) 2023 Ultra Librarian. All rights reserved.
